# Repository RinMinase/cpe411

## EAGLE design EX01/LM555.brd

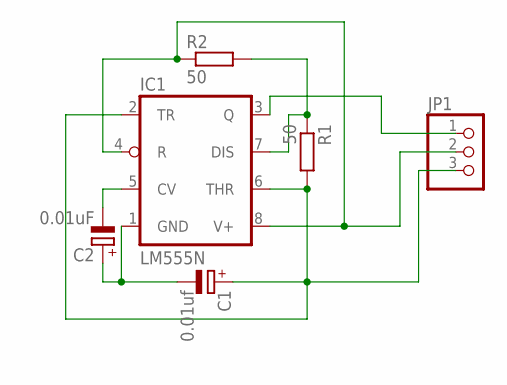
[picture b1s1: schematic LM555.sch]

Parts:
C1: 0.01uf; E2,5-6
C2: 0.01uF; E2,5-6
IC1: LM555N; DIL08
JP1: PINHD-1X3; 1X03
R1, R2: 50; 0207/10

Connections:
unnamed: IC1.7 (DIS), R1.1, R2.2
unnamed: C1.-, C2.+, IC1.1 (GND)
unnamed: C2.-, IC1.5 (CV)
unnamed: C1.+, IC1.2 (TR), IC1.6 (THR), JP1.3, R1.2
unnamed: IC1.4 (R), IC1.8 (V+), JP1.2, R2.1
unnamed: IC1.3 (Q), JP1.1

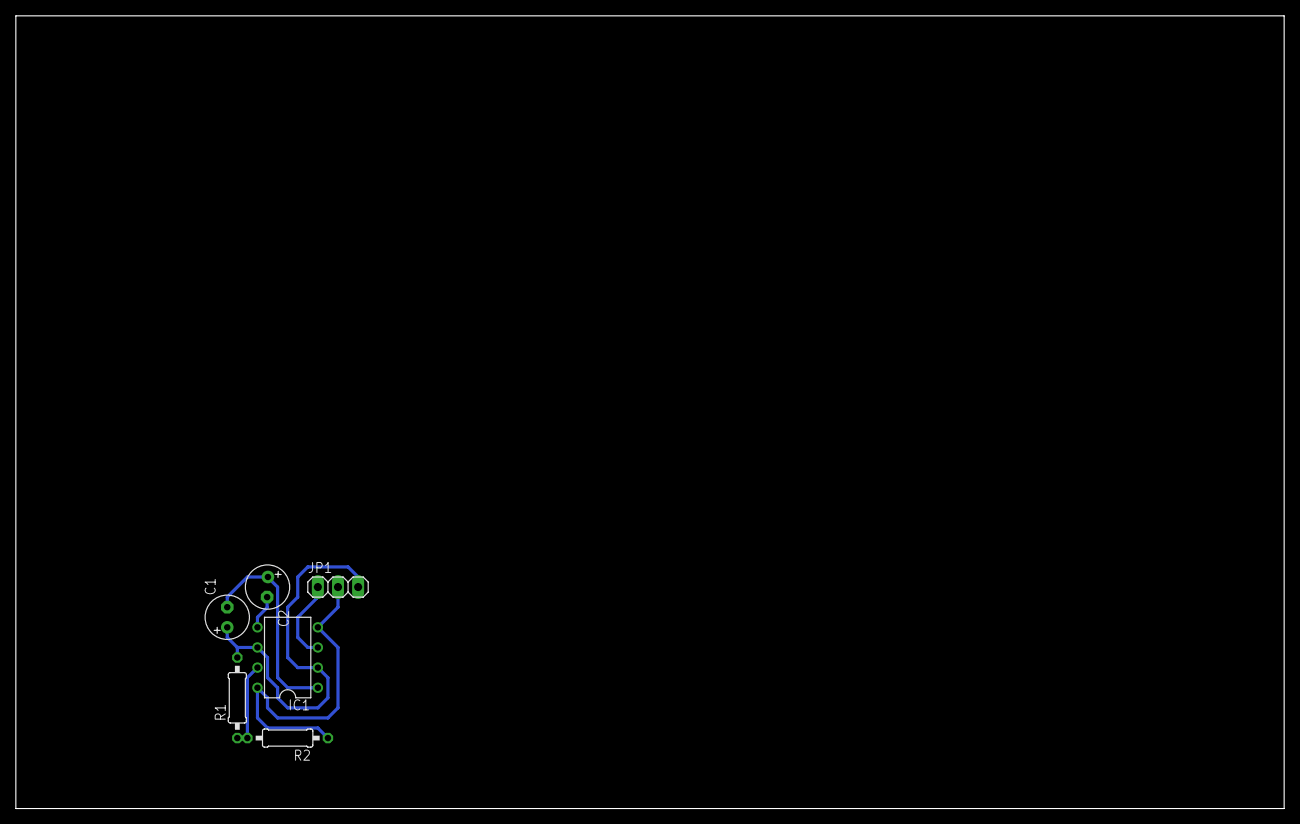
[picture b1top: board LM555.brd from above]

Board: 2 copper layers, 160.0 x 100.0 mm, 6 parts (0 on the bottom side), 6 nets.

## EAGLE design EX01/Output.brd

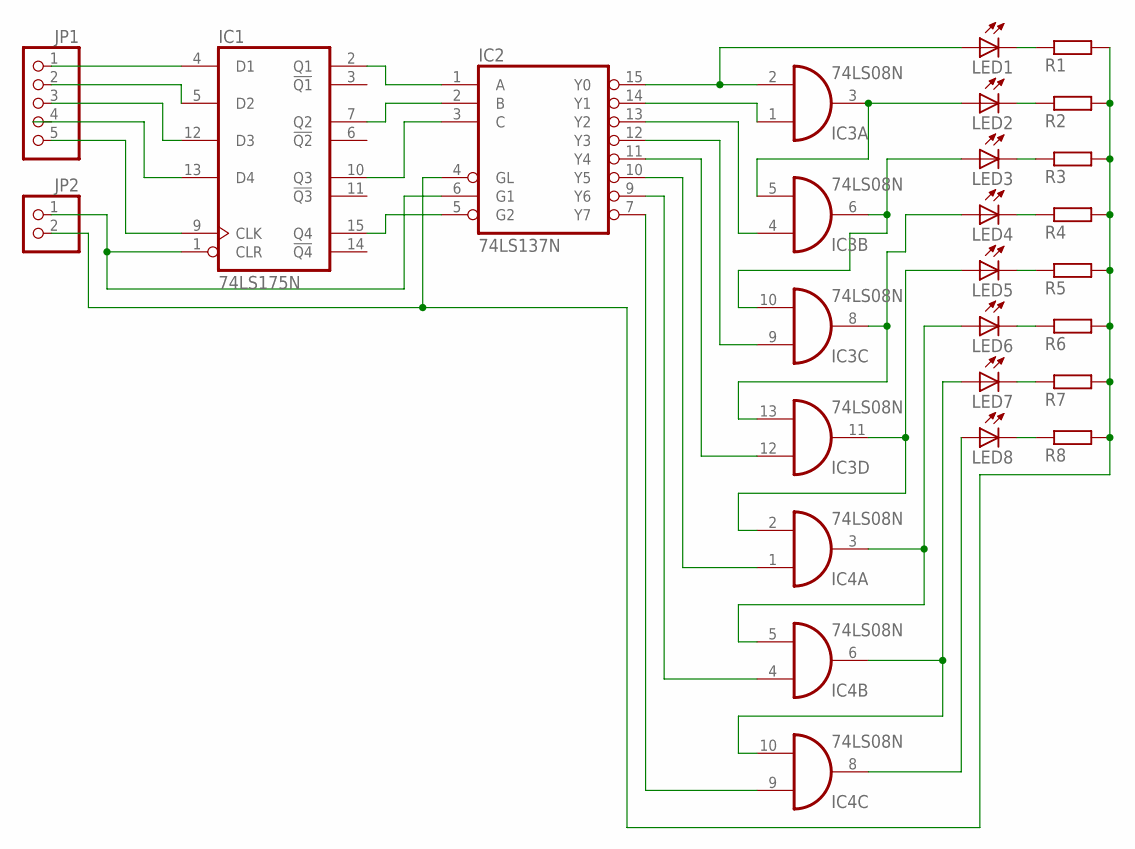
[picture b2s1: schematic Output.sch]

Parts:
IC1: 74LS175N; DIL16
IC2: 74LS137N; DIL16
IC3, IC4: 74LS08N; DIL14
JP1: PINHD-1X5; 1X05
JP2: PINHD-1X2; 1X02
LED1, LED2, LED3, LED4, LED5, LED6, LED7, LED8: LED5MM
R1, R2, R3, R4, R5, R6, R7, R8: R-EU_0207/10; 0207/10

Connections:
GND: IC1.8 (GND), IC2.8 (GND), IC3.7 (GND), IC4.7 (GND)
unnamed: IC1.4 (D1), JP1.1
unnamed: IC1.5 (D2), JP1.2
unnamed: IC1.12 (D3), JP1.3
unnamed: IC1.9 (CLK), JP1.5
unnamed: IC1.1 (CLR), IC2.6 (G1), JP2.1
unnamed: IC1.2 (Q1), IC2.1 (A)
unnamed: IC1.7 (Q2), IC2.2 (B)
unnamed: IC1.10 (Q3), IC2.3 (C)
unnamed: IC1.15 (Q4), IC2.5 (G2)
unnamed: IC2.4 (GL), JP2.2, R1.2, R2.2, R3.2, R4.2, R5.2, R6.2, R7.2, R8.2
unnamed: LED4.K (C), R4.1
unnamed: LED1.K (C), R1.1
unnamed: LED2.K (C), R2.1
unnamed: LED3.K (C), R3.1
unnamed: LED5.K (C), R5.1
unnamed: LED6.K (C), R6.1
unnamed: LED7.K (C), R7.1
unnamed: LED8.K (C), R8.1
unnamed: IC2.15 (Y0), IC3.2 (I1), LED1.A
unnamed: IC2.14 (Y1), IC3.1 (I0)
unnamed: IC3.3 (O), IC3.5 (I1), LED2.A
unnamed: IC2.13 (Y2), IC3.4 (I0)
unnamed: IC3.6 (O), IC3.10 (I1), LED3.A
unnamed: IC3.8 (O), IC3.13 (I1), LED4.A
unnamed: IC3.11 (O), IC4.2 (I1), LED5.A
unnamed: IC4.3 (O), IC4.5 (I1), LED6.A
unnamed: IC4.6 (O), IC4.10 (I1), LED7.A
unnamed: IC4.8 (O), LED8.A
unnamed: IC2.12 (Y3), IC3.9 (I0)
unnamed: IC2.11 (Y4), IC3.12 (I0)
unnamed: IC2.10 (Y5), IC4.1 (I0)
unnamed: IC2.9 (Y6), IC4.4 (I0)
unnamed: IC2.7 (Y7), IC4.9 (I0)
VCC: IC1.16 (VCC), IC2.16 (VCC), IC3.14 (VCC), IC4.14 (VCC)

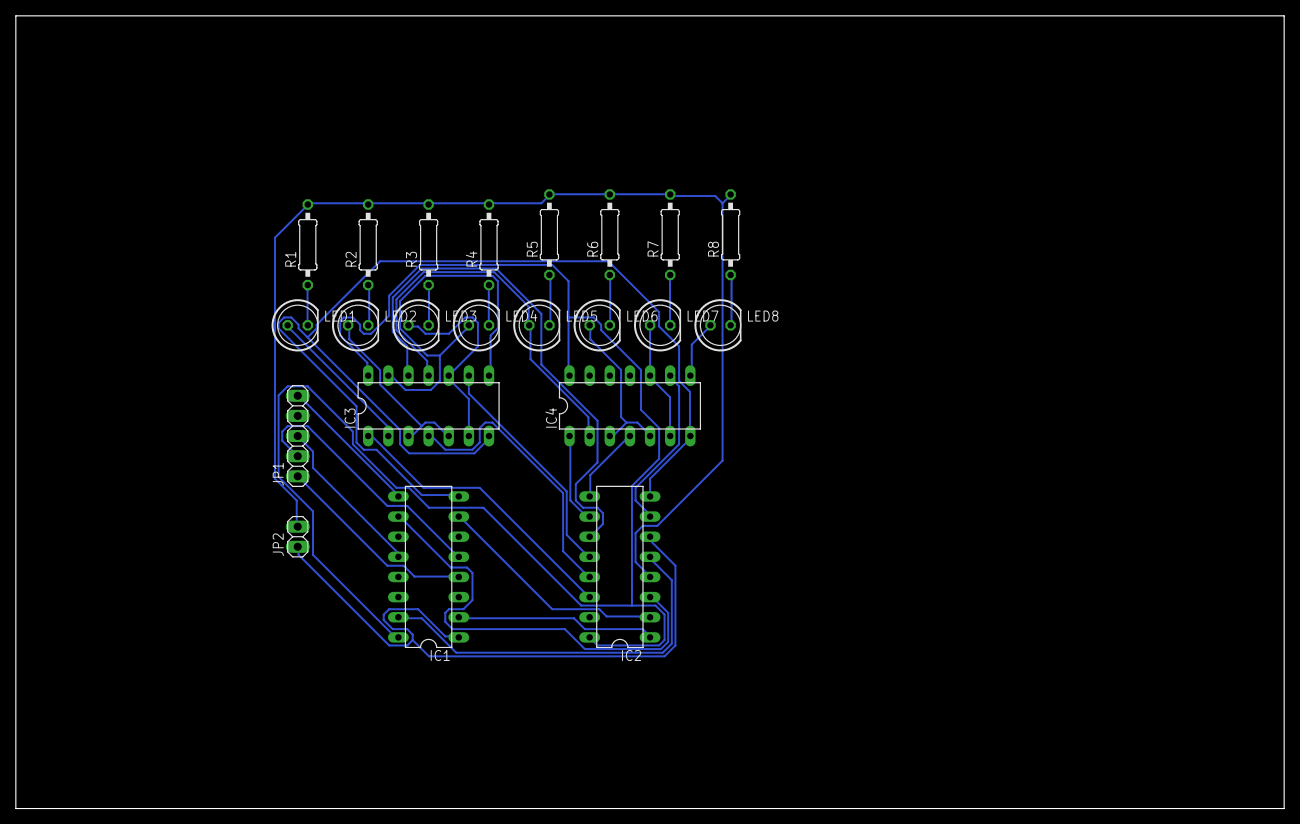
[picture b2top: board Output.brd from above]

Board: 2 copper layers, 160.0 x 100.0 mm, 22 parts (0 on the bottom side), 35 nets.

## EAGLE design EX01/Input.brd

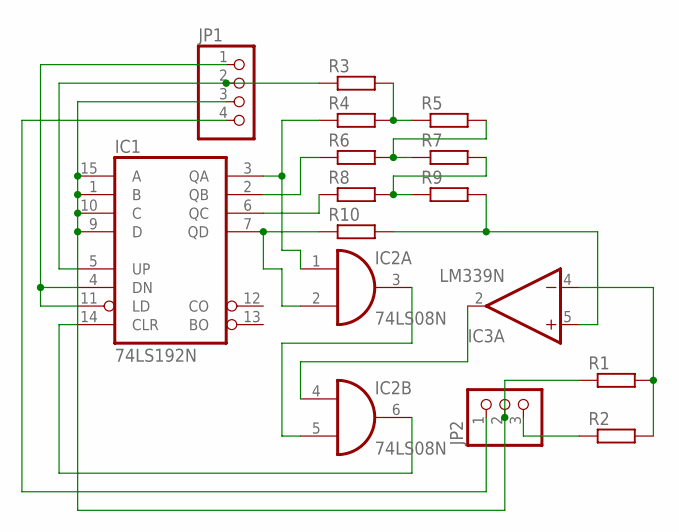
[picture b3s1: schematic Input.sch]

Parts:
IC1: 74LS192N; DIL16
IC2: 74LS08N; DIL14
IC3: LM339N; DIL14
JP1: PINHD-1X4; 1X04
JP2: PINHD-1X3; 1X03
R1, R2, R3, R4, R5, R6, R7, R8, R9, R10: R-EU_0207/10; 0207/10

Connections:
GND: IC1.8 (GND), IC2.7 (GND), IC3.12 (GND)
unnamed: IC3.5 (+IN), R9.2, R10.2
unnamed: IC1.3 (QA), IC2.1 (I0), R4.1
unnamed: IC2.3 (O), IC2.5 (I1)
unnamed: IC1.14 (CLR), IC2.6 (O)
unnamed: IC1.5 (UP), JP1.2, R3.1
unnamed: IC1.4 (DN), IC1.11 (LD), JP1.1
unnamed: IC1.1 (B), IC1.9 (D), IC1.10 (C), IC1.15 (A), JP1.3, JP2.2, R1.1
unnamed: IC2.4 (I0), IC3.2 (OUT)
unnamed: IC3.4 (-IN), R1.2, R2.2
unnamed: JP2.3, R2.1
unnamed: JP1.4, JP2.1
unnamed: R7.2, R8.2, R9.1
unnamed: R5.2, R6.2, R7.1
unnamed: R3.2, R4.2, R5.1
unnamed: IC1.6 (QC), R8.1
unnamed: IC1.2 (QB), R6.1
unnamed: IC1.7 (QD), IC2.2 (I1), R10.1
V+: IC3.3 (V+)
VCC: IC1.16 (VCC), IC2.14 (VCC)

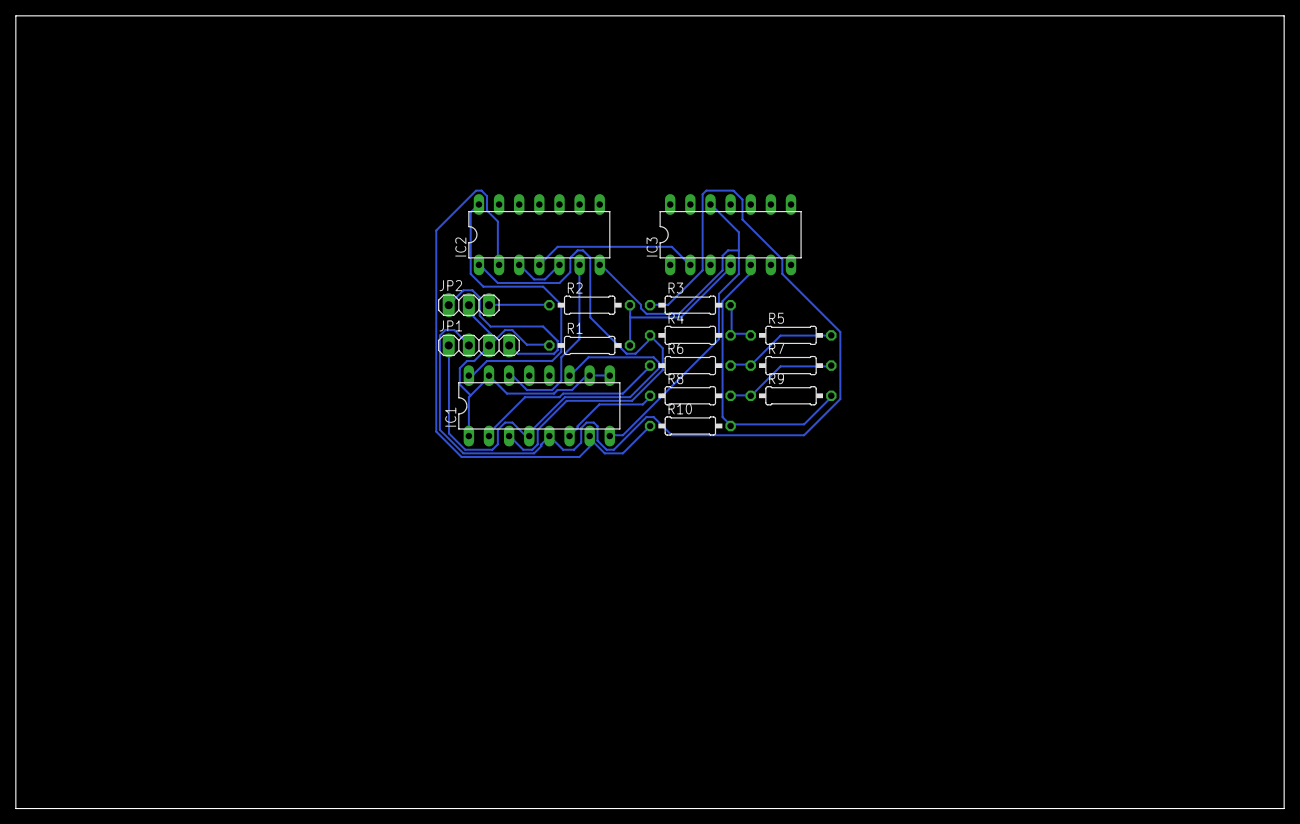
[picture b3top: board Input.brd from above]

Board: 2 copper layers, 160.0 x 100.0 mm, 15 parts (0 on the bottom side), 19 nets.

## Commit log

2019-10-20 Added exercise 1
